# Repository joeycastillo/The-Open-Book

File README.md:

# The Open Book: Project Reboot

**A note from the project creator:** The Open Book was my first real electronics project; the earliest designs date to late 2019. I have learned a lot since those early days, and as such, here three years later, I am hitting reset. At this time the repository contains a version of the Open Book designed around the Raspberry Pi Pico. It's optimized for low part count and easy hand assembly, but it runs on AAA batteries and may not be as svelte as some folks might prefer. At a later date, I hope to design a followup with built-in LiPo charging and a slimmer profile, but at this time, this version of the book is the quickest path to getting hardware in people's hands so that we can start hacking on firmware together.

For details on how to build, test and use Open Book, I've [made documentation available here](https://www.oddlyspecificobjects.com/projects/openbook/).

The original Open Book repository has been archived in a branch called [original](https://github.com/joeycastillo/The-Open-Book/tree/original).

[The Open Book firmware, called libros, is under development here](https://github.com/joeycastillo/libros). It's a goddamn mess in some ways, and in dire need of some documentation, but for the moment it does do the job of presenting a list of books stored on an SD card, and letting you read them. The canonical format for books is plain text with the book title on the first line, OR plain text plus some front matter and some ASCII control codes for chapter breaks and formatting, [as documented here](https://www.oddlyspecificobjects.com/projects/openbook/#advanced-text-formatting).

## Original Introduction

As a society, we need an open source device for reading. Books are among the most important documents of our culture, yet the most popular and widespread devices we have for reading — the Kobo, the Nook, the Kindle and even the iPad — are closed devices, operating as small moving parts in a set of giant closed platforms whose owners' interests are not always aligned with readers'.

The Open Book aims to be a simple device that anyone with a soldering iron can build for themselves. The Open Book should be comprehensible: the reader should be able to look at it and understand, at least in broad strokes, how it works. It should be extensible, so that a reader with different needs can write code and add accessories that make the book work for them. It should be global, supporting readers of books in all the languages of the world. Most of all, it should be open, so that anyone can take this design as a starting point and use it to build a better book.

## State of the Book

At this time, the Pi Pico book is in decent shape if you want to try your hand at building it yourself. You will need to have two custom things fabricated: the **Open Book Main Board** (which you can get as a bare PCB) and the **Castellated E-Paper Driver** module (which you'll want to have done as a PCBA job). All the files you will need to send out for this can be found in the **Fabrication Files** folder in the project root:

* Upload `OSO-BOOK-C1-04-rounded.zip` to your PCB fabrication house of choice. It is designed to be a two-layer, 1 mm thick PCB, and you can use either an ENIG or lead-free HASL finish.
* If you plan to use JLCPCB's economic PCBA service, upload all three files in `OSO-BOOK-C2-01` to JLCPCB. Opt for a 1 mm thick lead-free HASL finish. Note that the board is slightly wider than it needs to be, just to meet the minimum size requirements for this service.
* If you plan to use PCBWay's PCBA service, upload all three files in `OSO-BOOK-C2-02` to PCBWay. Once again, opt for a 1 mm thick lead-free HASL finish. 

Other Parts: 

* Two of these [side mount buttons](https://www.digikey.com/en/products/detail/würth-elektronik/434351045816/5209090)
* One of these [side-mount switches](https://www.digikey.com/en/products/detail/c-k/JS102011SAQN/1640095)
* One [MEM2075 MicroSD card slot](https://www.digikey.com/en/products/detail/gct/MEM2075-00-140-01-A/9859614)
* One [GD25Q16C Flash chip](https://www.digikey.com/en/products/detail/gigadevice-semiconductor-hk-limited/GD25Q16CTIGR/9484675) with SOIC / SOP8 footprint.
* One [Keystone 1022 dual AAA battery holder](https://www.digikey.com/en/products/detail/keystone-electronics/1022/2137859) (you can get clones on Aliexpress for cheap)
* Two P-channel MOSFETS with SOT23 footprint (I use the DMG3415)
* Two 10kΩ resistors with 1206 footprint.
* Two 10µF capacitors with 1206 footprint (rated voltage >=6.3V).
* One 1µF capacitor with 0805 footprint (rated voltage >=6.3V).
* Seven through-hole slim tactile buttons (3mm by 6mm; [TL1107 type](https://www.digikey.com/en/products/detail/e-switch/TL1107AF130WQ/378976))
* One [GDEW042T2 grayscale e-paper display](https://buy-lcd.com/products/42inch-e-inkanel-spi-interface-buy-eaper-display). (Don't get the tri-color version; it'll end in heartbreak)
* And finally, one [Raspberry Pi Pico](https://www.digikey.com/en/products/detail/raspberry-pi/SC0915/13624793) board

The Open Book is open source hardware: you should feel free to build one yourself, order parts for ten and do a workshop at your local maker space, or even buy parts for fifty and sell them as kits. 

Please steal this book.

I plan to add more documentation in the new year, but until then, [this half-hour video walks through building one Open Book board in real-time](https://archive.org/details/live-from-the-oddly-specific-kitchen-table-assembling-the-pcbway-official-sponso).

### Forking and tweaking the boards

* Design files for the Open Book main board can be found in the `OSO-BOOK-C1` folder. It's a KiCad project.
* Design files for the castellated e-paper driver module can be found in the `OSO-BOOK-C2` folder. Alas, they are Eagle projects that predate my move to KiCad. There are two versions: an older version that was successfully fabricated with JLCPCB's economic PCBA service (`OSO-BOOK-C2-01`), and a newer version successfully fabricated using PCBWay's PCBA service (`OSO-BOOK-C2-02`). Both work great.

## License

 Different components of the project are licensed differently, see [LICENSE.md](https://github.com/joeycastillo/The-Open-Book/blob/main/LICENSE.md).

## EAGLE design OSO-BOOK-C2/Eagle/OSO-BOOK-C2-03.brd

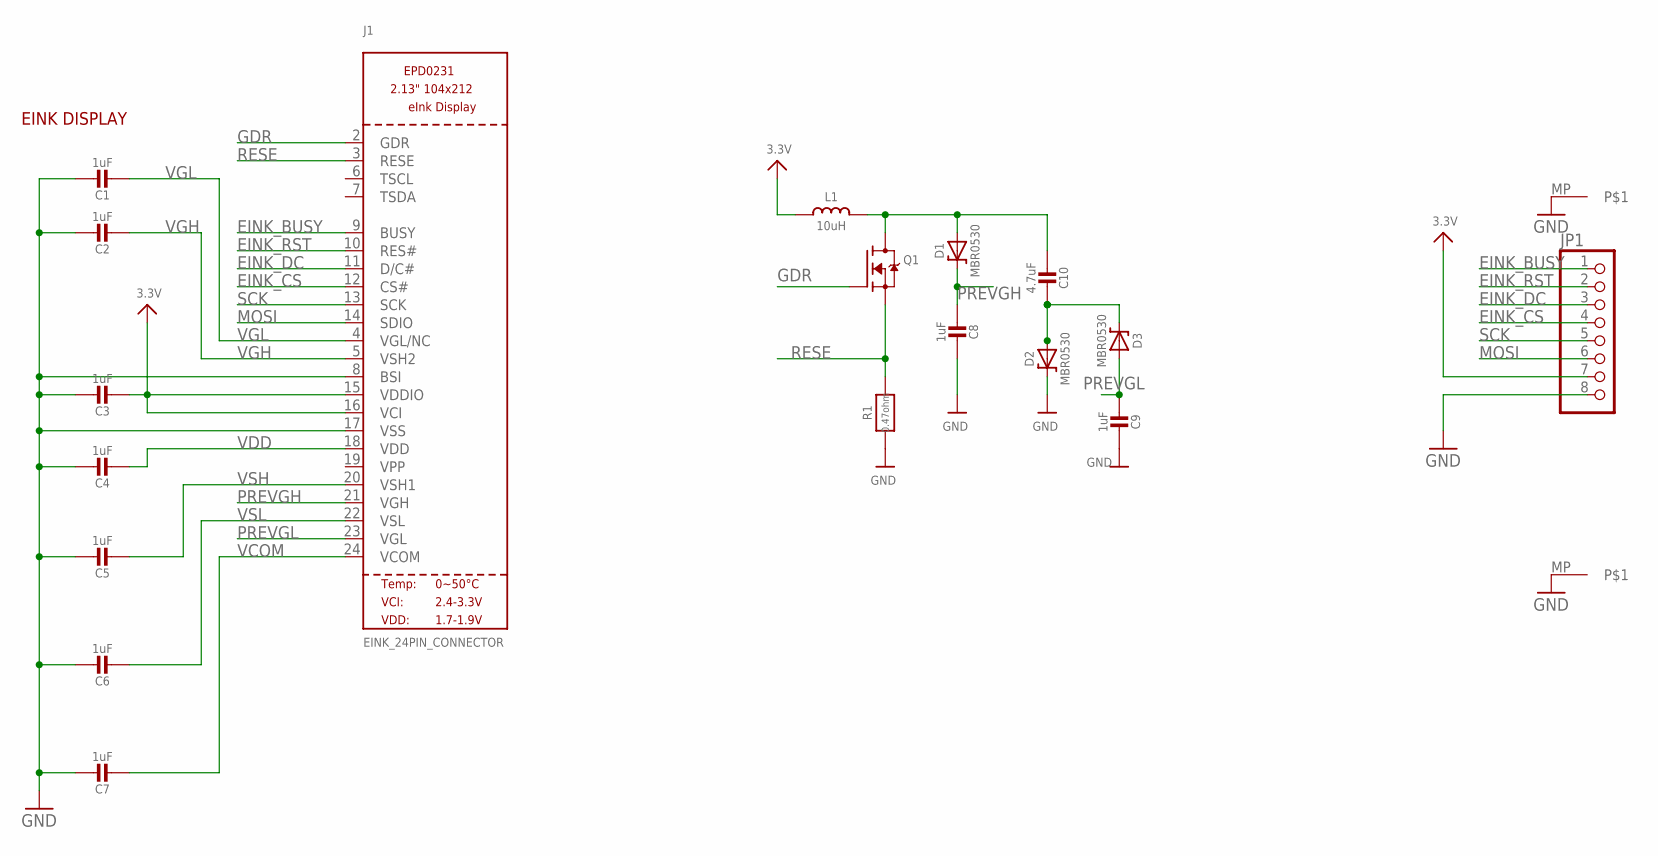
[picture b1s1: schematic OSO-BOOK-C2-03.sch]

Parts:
C1, C2, C3, C4, C5, C6, C7, C8, C9: 1uF; 0805-NO
C10: 4.7uF; 0805-NO
D1, D2, D3: MBR0530; SOD-123
J1: EINK_24PIN_CONNECTOR; EINK_24PIN
JP1: HEADER-1X8ROUND76; 1X08_ROUND_76
L1: 10uH; MICROBUILDER__0805
Q1: IRLML0100; SOT23-3
R1: 0.47ohm; _0402
U$2, U$3: BIGOVAL

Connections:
3.3V: C3.2, J1.15 (VDDIO), J1.16 (VCI), JP1.7, L1.1
EINK_BUSY: J1.9 (BUSY), JP1.1
EINK_CS: J1.12 (CS#), JP1.4
EINK_DC: J1.11 (D/C#), JP1.3
EINK_RST: J1.10 (RES#), JP1.2
GDR: J1.2 (GDR), Q1.1 (G)
GND: C1.1, C2.1, C3.1, C4.1, C5.1, C6.1, C7.1, C8.2, C9.2, D2.C, J1.8 (BSI), J1.17 (VSS), JP1.8, R1.2, U$2.MP, U$3.MP
MOSI: J1.14 (SDIO), JP1.6
unnamed: C10.2, D2.A, D3.C
unnamed: C10.1, D1.A, L1.2, Q1.3 (D)
PREVGH: C8.1, D1.C, J1.21 (VGH)
PREVGL: C9.1, D3.A, J1.23 (VGL)
RESE: J1.3 (RESE), Q1.2 (S), R1.1
SCK: J1.13 (SCK), JP1.5
VCOM: C7.2, J1.24 (VCOM)
VDD: C4.2, J1.18 (VDD)
VGH: C2.2, J1.5 (VSH2)
VGL: C1.2, J1.4 (VGL/NC)
VSH: C5.2, J1.20 (VSH1)
VSL: C6.2, J1.22 (VSL)

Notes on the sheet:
EINK DISPLAY

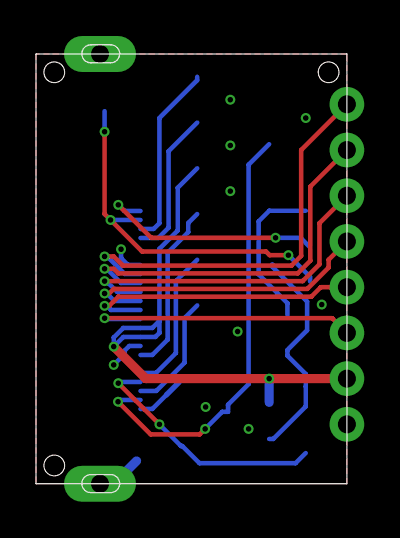
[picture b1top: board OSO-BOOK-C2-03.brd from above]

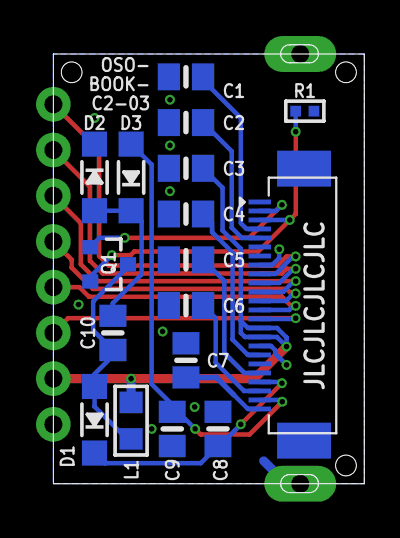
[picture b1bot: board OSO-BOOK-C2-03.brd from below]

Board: 2 copper layers, 17.3 x 24.9 mm, 20 parts (17 on the bottom side), 20 nets.

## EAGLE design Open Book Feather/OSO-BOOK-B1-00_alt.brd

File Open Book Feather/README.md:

# Notes on the Open Book PCB files

The current working, tested revision is **Open Book A1 Rev 06** (**OSO-BOOK-A1-06**). For the sake of clarity, I've removed revisions 01 through 04; if you made one of these old boards, these notes remain.

## Open Book A1 Rev 01 Errata

I imagine you don't have this board; it was the first test, and was replaced with revision 2 almost immediately. It had a couple of big issues:

* The buttons on the shift register floated, because there were no pull-up resistors. This rendered the buttons unusable.
* The Neopixel, in addition to being in a really inconvenient place, was powered by VHI instead of the 3V regulator, which made it power up before everything else and shine bright blue until you took control of it. It also wouldn't turn off when the enable switch was thrown.

## Open Book A1 Rev 02 Errata

There are two errors on this revision's descriptive silkscreen: first, at the bottom, in the "Button Register" block, the shift register's pins are listed as:

    Pins: 
    BUTTON_LATCH: D48/PB31
    BUTTON_OUT:  D49/PB30
    BUTTON_CLOCK: D50/PB00

The correct mapping is:

    Pins: 
    BUTTON_LATCH: D50/PB00
    BUTTON_OUT:  D49/PB30
    BUTTON_CLOCK: D48/PB31

Second, the SAM D51 Microcontroller block erroneously lists the UART's SERCOM as SERCOM0. It is in fact SERCOM5.

## Open Book A1 Rev 03

Revision 3 was never fabricated; it simply fixed the first error above, but was otherwise identical to Revision 2. I wanted to correct the error in case anyone was building along at home, and bumped the revision to make it clear which version had the issue. It still has the incorrect SERCOM listed, though; that was not caught until later.

Note that the pin muxing changed after revision 3; if you have board revision A1-01, A1-02 or A1-03, you will need to set a flag when compiling your code. In the Arduino IDE, this setting is in `Tools -> Hardware Revision`. In CircuitPython, you can just use the digital pin numbers as labeled on your silkscreen to access the correct pins.

## Open Book A1 Rev 04

This board has the final pinout (no need to set the Hardware Revision flag), and adds several features:

* Microphone shutdown pin
* USB voltage monitor (detect when plugged in to external power)
* Battery full indicator

This is the last revision with the SERCOM0/SERCOM5 silkscreen error.

## Open Book A1 Rev 05

This is identical to Rev 04, but fixes the silkscreen error in the SAM D51 block. It also adds a RC filter to the USB cable shield (recommendation from the SAM D51 data sheet), and tweaks the through-hole button footprints for a slightly better fit.

This version works quite well. If you have this version, there is no need to get the A1-06 version.

## Open Book A1 Rev 06

This is the final version of the A1-type hardware. It adds pull-up resistors for the Babel Flash chip and MicroSD card, and bias resistors for the audio output on the headphone jack.

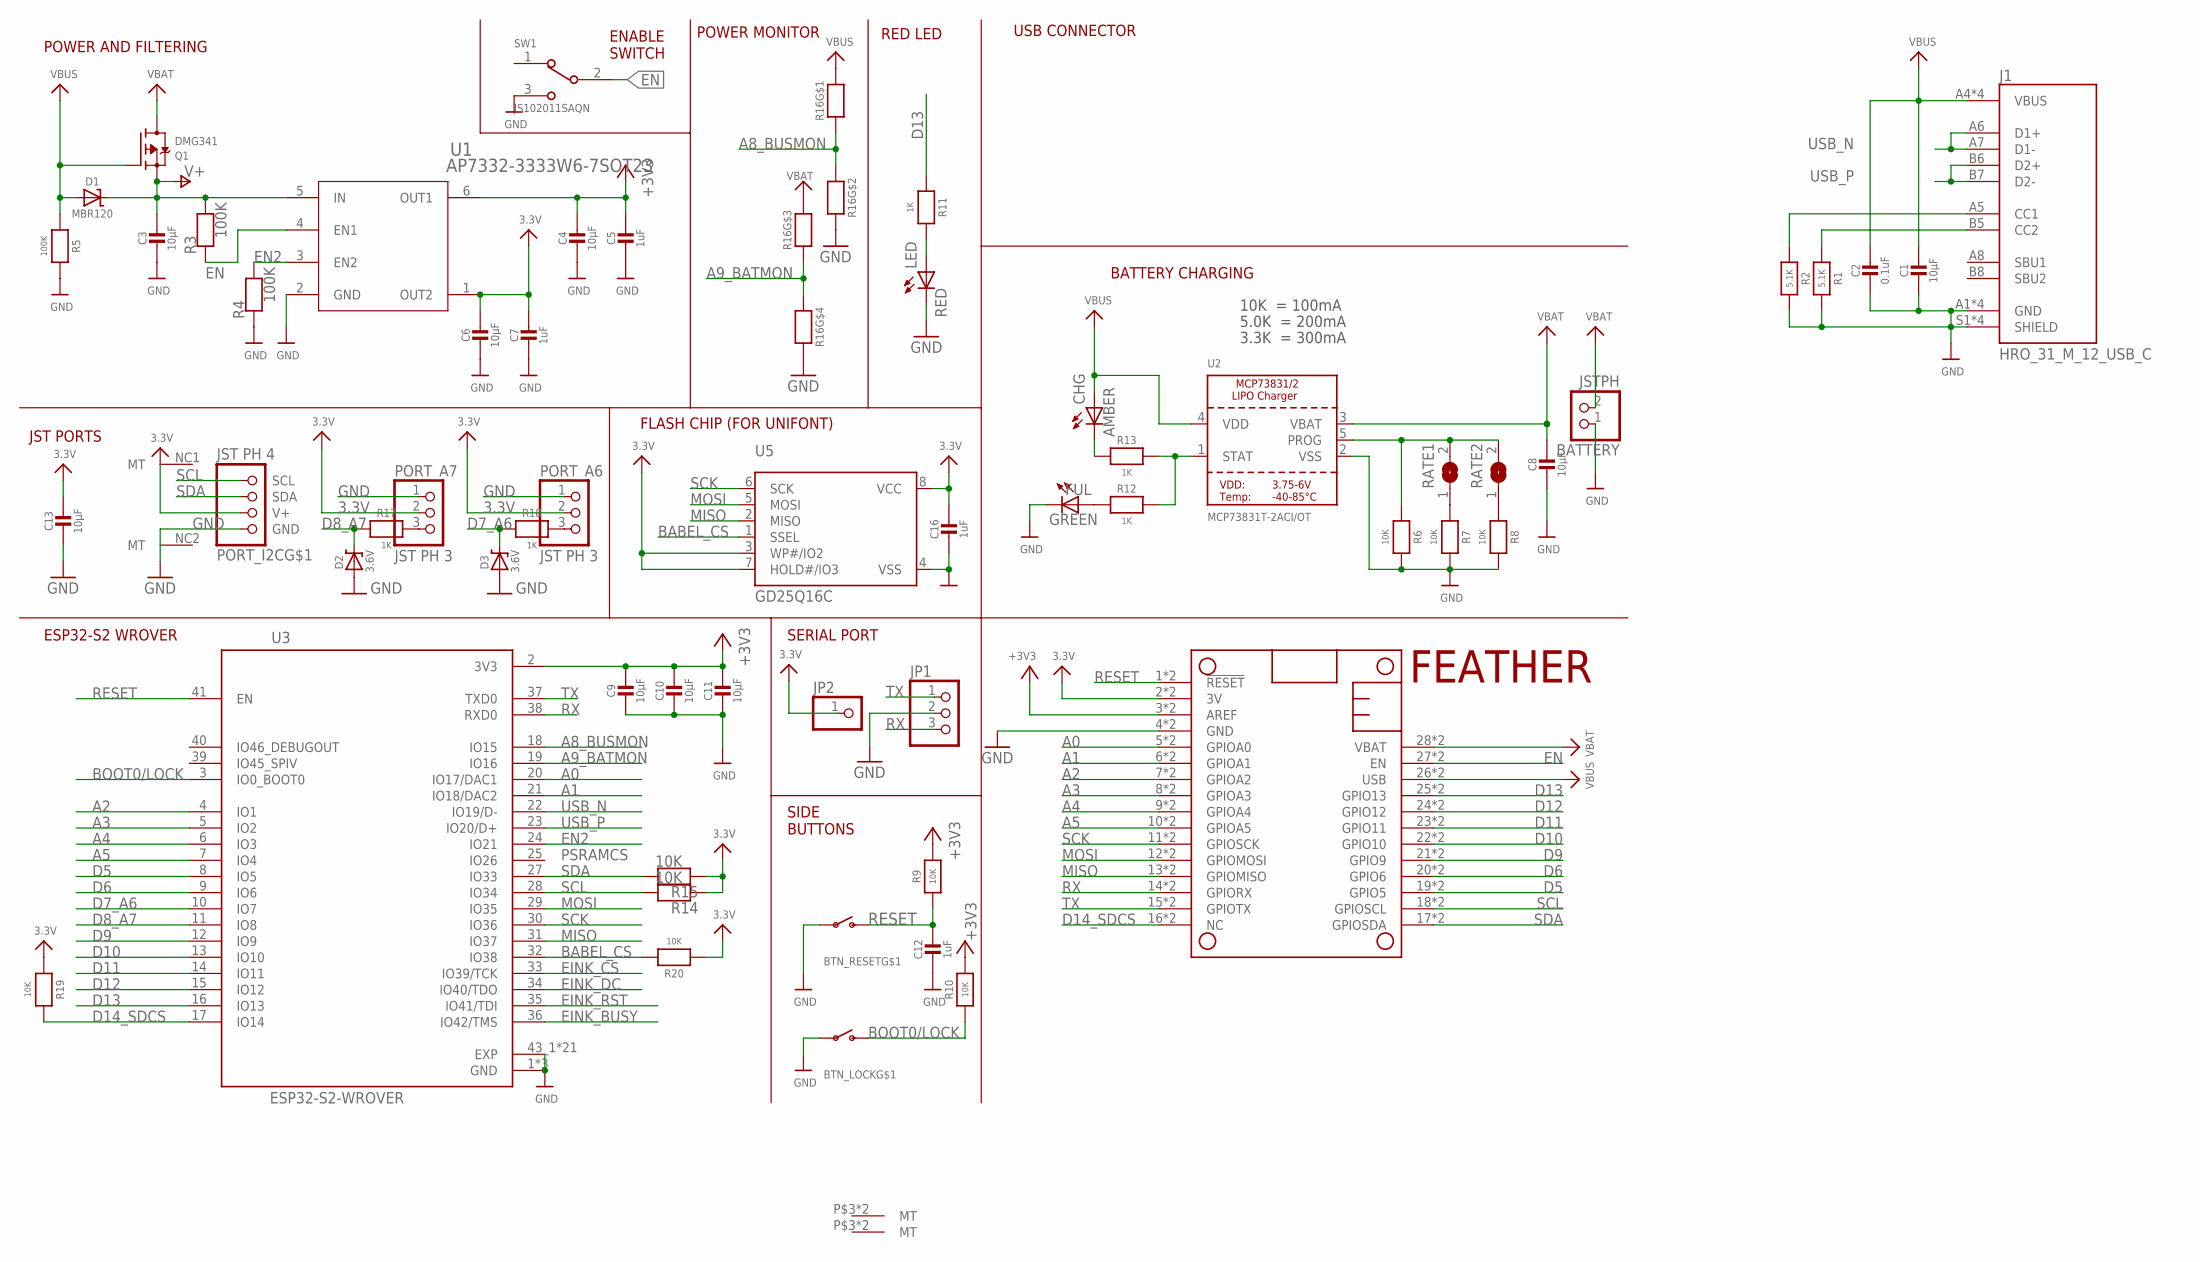
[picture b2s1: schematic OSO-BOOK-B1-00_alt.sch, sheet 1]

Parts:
BATTERY: JSTPH; JSTPH2
BTN_LOCK: SWITCH_SPSTTL3330A; TL3330A
BTN_RESET: SWITCH_SPSTTL3330A; TL3330A
C1, C3, C4, C6, C8, C9, C10, C11, C13: 10µF; 0805-NO
C2: 0.1uF; 0805-NO
C5, C7, C12, C16: 1uF; 0805-NO
CHG: AMBER; CHIP-LED0805
D1: MBR120; SOD-123
D2, D3: 3.6V; SOD-123
FUL: GREEN; CHIP-LED0805
J1: HRO_31_M_12_USB_C
JP1: PINHD-1X3; 1X03
JP2: PINHD-1X1; 1X01
LED: RED; CHIP-LED0805
MS1: FEATHERWING_SMTDUALNOHOLES; FEATHERWING_SMT_NOHOLES
PORT_A6, PORT_A7: JST PH 3; JSTPH3
PORT_I2C: JST PH 4; JSTPH4
Q1: DMG341; SOT23-R
R1, R2: 5.1K; 0805-NO
R3, R4, R5: 100K; 0805-NO
R6, R7, R8, R9, R10, R14, R15, R19, R20: 10K; 0805-NO
R11, R12, R13, R17, R18: 1K; 0805-NO
R16: EXB-V8V103JV-GOOD; EXBV8V
RATE1, RATE2: SOLDERJUMPER; SOLDERJUMPER_ARROW_NOPASTE
SW1: JS102011SAQN; SW_JS102011SAQN
U1: AP7332-3333W6-7SOT23; SOT23-6
U2: MCP73831T-2ACI/OT; SOT23-5
U3: ESP32-S2-WROVER; MODULE_ESP32-S2-WROVER
U5: GD25Q16C; MICROBUILDER_SOIC8_150MIL

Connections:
3.3V: C6.1, C7.1, C13.1, C16.1, JP2.1, MS1.2 (3V), MS1.2B (3V), PORT_A6.2, PORT_A7.2, PORT_I2C.2 (V+), R14.1, R15.1, R19.1, R20.1, U1.1 (OUT2), U5.3 (WP#/IO2), U5.7 (HOLD#/IO3), U5.8 (VCC); also elsewhere on the board
+3V3: C4.1, C5.1, C9.1, C10.1, C11.1, MS1.3 (AREF), MS1.3B (AREF), R9.2, R10.2, U1.6 (OUT1), U3.2 (3V3)
A0: MS1.5 (GPIOA0), MS1.5B (GPIOA0), U3.20 (IO17/DAC1)
A1: MS1.6 (GPIOA1), MS1.6B (GPIOA1), U3.21 (IO18/DAC2)
A2: MS1.7 (GPIOA2), MS1.7B (GPIOA2), U3.4 (IO1)
A3: MS1.8 (GPIOA3), MS1.8B (GPIOA3), U3.5 (IO2)
A4: MS1.9 (GPIOA4), MS1.9B (GPIOA4), U3.6 (IO3)
A5: MS1.10 (GPIOA5), MS1.10B (GPIOA5), U3.7 (IO4)
A6: PORT_A6.3, R18.1
A7: PORT_A7.3, R17.1
A8_BUSMON: R16.1, R16.2 (1), U3.18 (IO15)
A9_BATMON: R16.3 (1), R16.4 (1), U3.19 (IO16)
BABEL_CS: R20.2, U3.32 (IO38), U5.1 (SSEL)
BOOT0/LOCK: BTN_LOCK.P$2 (S), R10.1, U3.3 (IO0_BOOT0)
D5: MS1.19 (GPIO5), MS1.19B (GPIO5), U3.8 (IO5)
D6: MS1.20 (GPIO6), MS1.20B (GPIO6), U3.9 (IO6)
D7_A6: D3.C, R18.2, U3.10 (IO7)
D8_A7: D2.C, R17.2, U3.11 (IO8)
D9: MS1.21 (GPIO9), MS1.21B (GPIO9), U3.12 (IO9)
D10: MS1.22 (GPIO10), MS1.22B (GPIO10), U3.13 (IO10)
D11: MS1.23 (GPIO11), MS1.23B (GPIO11), U3.14 (IO11)
D12: MS1.24 (GPIO12), MS1.24B (GPIO12), U3.15 (IO12)
D13: MS1.25 (GPIO13), MS1.25B (GPIO13), R11.1, U3.16 (IO13)
D14_SDCS: MS1.16 (NC), MS1.16B (NC), R19.2, U3.17 (IO14); also elsewhere on the board
EINK_BUSY: U3.36 (IO42/TMS); also elsewhere on the board
EINK_CS: U3.33 (IO39/TCK); also elsewhere on the board
EINK_DC: U3.34 (IO40/TDO); also elsewhere on the board
EINK_RST: U3.35 (IO41/TDI); also elsewhere on the board
EN: MS1.27 (EN), MS1.27B (EN), R3.1, SW1.2, U1.4 (EN1)
EN2: R4.2, U1.3 (EN2), U3.24 (IO21)
GND: BATTERY.1, BTN_LOCK.P$1, BTN_RESET.P$1, C1.2, C2.2, C3.2, C4.2, C5.2, C6.2, C7.2, C8.2, C9.2, C10.2, C11.2, C12.2, C13.2, C16.2, D2.A, D3.A, FUL.C, J1.A1 (GND), J1.A12 (GND), J1.B1 (GND), J1.B12 (GND), J1.S1 (SHIELD), J1.S2 (SHIELD), J1.S3 (SHIELD), J1.S4 (SHIELD), JP1.2, LED.C, MS1.4 (GND), MS1.4B (GND), PORT_A6.1, PORT_A7.1, PORT_I2C.1 (GND), R1.2, R2.2, R4.1, R5.2, R6.2, R7.2, R8.2, R16.5 (2), R16.7 (2), SW1.3, U1.2 (GND), U2.2 (VSS), U3.1 (GND), U3.26 (GND), U3.42 (GND), U3.43_1 (EXP), U3.43_2 (EXP), U3.43_3 (EXP), U3.43_4 (EXP), U3.43_5 (EXP), U3.43_6 (EXP), U3.43_7 (EXP), U3.43_8 (EXP), U3.43_9 (EXP), U3.43_10 (EXP), U3.43_11 (EXP), U3.43_12 (EXP), U3.43_13 (EXP), U3.43_14 (EXP), U3.43_15 (EXP), U3.43_16 (EXP), U3.43_17 (EXP), U3.43_18 (EXP), U3.43_19 (EXP), U3.43_20 (EXP), U3.43_21 (EXP), U5.4 (VSS); also elsewhere on the board
MISO: MS1.13 (GPIOMISO), MS1.13B (GPIOMISO), U3.31 (IO37), U5.2 (MISO); also elsewhere on the board
MOSI: MS1.12 (GPIOMOSI), MS1.12B (GPIOMOSI), U3.29 (IO35), U5.5 (MOSI); also elsewhere on the board
unnamed: R7.1, RATE1.1
unnamed: CHG.C, R13.1
unnamed: R8.1, RATE2.1
unnamed: LED.A, R11.2
unnamed: FUL.A, R12.1
unnamed: J1.B5 (CC2), R1.1
unnamed: J1.A5 (CC1), R2.1
PROG: R6.1, RATE1.2, RATE2.2, U2.5 (PROG)
RESET: BTN_RESET.P$2 (S), C12.1, MS1.1 (!RESET), MS1.1B (!RESET), R9.1, U3.41 (EN)
RX: JP1.3, MS1.14 (GPIORX), MS1.14B (GPIORX), U3.38 (RXD0)
SCK: MS1.11 (GPIOSCK), MS1.11B (GPIOSCK), U3.30 (IO36), U5.6 (SCK); also elsewhere on the board
SCL: MS1.18 (GPIOSCL), MS1.18B (GPIOSCL), PORT_I2C.4 (SCL), R14.2, U3.28 (IO34); also elsewhere on the board
SDA: MS1.17 (GPIOSDA), MS1.17B (GPIOSDA), PORT_I2C.3 (SDA), R15.2, U3.27 (IO33); also elsewhere on the board
STAT: R12.2, R13.2, U2.1 (STAT)
TX: JP1.1, MS1.15 (GPIOTX), MS1.15B (GPIOTX), U3.37 (TXD0)
USB_N: J1.A6 (D1+), J1.A7 (D1-), U3.22 (IO19/D-)
USB_P: J1.B6 (D2+), J1.B7 (D2-), U3.23 (IO20/D+)
V+: C3.1, D1.C, Q1.2 (S), R3.2, U1.5 (IN)
VBAT: BATTERY.2, C8.1, MS1.28 (VBAT), MS1.28B (VBAT), Q1.3 (D), R16.6 (2), U2.3 (VBAT)
VBUS: C1.1, C2.1, CHG.A, D1.A, J1.A4 (VBUS), J1.A9 (VBUS), J1.B4 (VBUS), J1.B9 (VBUS), MS1.26 (USB), MS1.26B (USB), Q1.1 (G), R5.1, R16.8 (2), U2.4 (VDD)

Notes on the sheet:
FEATHER
POWER AND FILTERING
10K = 100mA
5.0K = 200mA
3.3K = 300mA
BATTERY CHARGING
USB CONNECTOR
POWER MONITOR
PSRAMCS
FLASH CHIP (FOR UNIFONT)
SERIAL PORT
RED LED
ENABLE SWITCH
SIDE BUTTONS
JST PORTS
ESP32-S2 WROVER

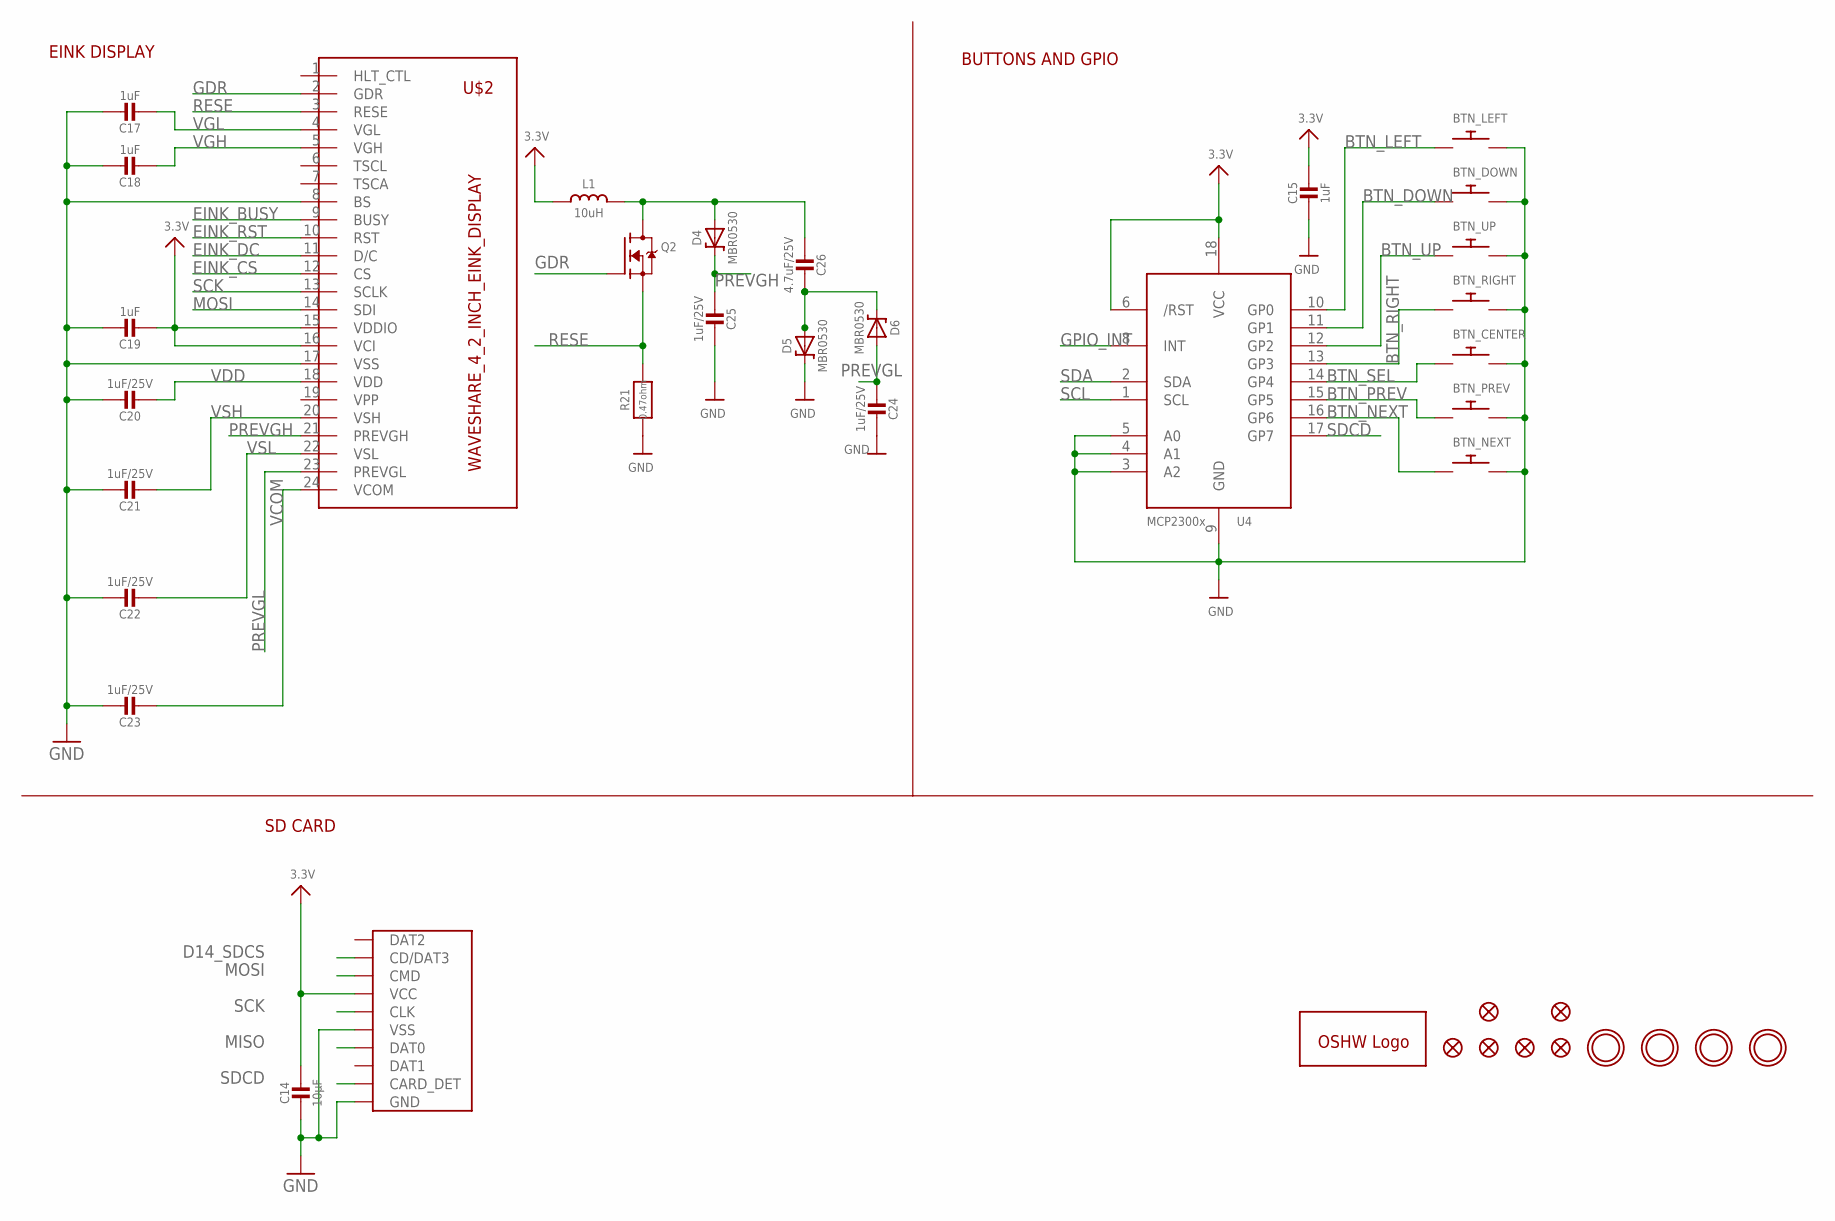
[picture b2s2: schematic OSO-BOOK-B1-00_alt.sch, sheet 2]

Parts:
BTN_CENTER: SWITCH_PUSHBUTTON_3.5X6MM; TACTILE_3X6MM
BTN_DOWN: SWITCH_PUSHBUTTON_3.5X6MM; TACTILE_3X6MM
BTN_LEFT: SWITCH_PUSHBUTTON_3.5X6MM; TACTILE_3X6MM
BTN_NEXT: SWITCH_PUSHBUTTON_3.5X6MM; TACTILE_3X6MM
BTN_PREV: SWITCH_PUSHBUTTON_3.5X6MM; TACTILE_3X6MM
BTN_RIGHT: SWITCH_PUSHBUTTON_3.5X6MM; TACTILE_3X6MM
BTN_UP: SWITCH_PUSHBUTTON_3.5X6MM; TACTILE_3X6MM
C14: 10µF; 0805-NO
C15, C17, C18, C19: 1uF; 0805-NO
C20, C21, C22, C23, C24, C25: 1uF/25V; 0805-NO
C26: 4.7uF/25V; 0805-NO
D4, D5, D6: MBR0530; SOD-123
FID1, FID2, FID3, FID4, FID5, FID6: FIDUCIAL_1MM
GOLD_ORB_SM1: OSHWLOGOLOGO5MM; OSHW_5MM
L1: 10uH; MICROBUILDER_INDUCTOR_4X4MM_NR401_BIGPADS
Q2: IRLML0100; SOT23-3
R21: 0.47ohm; 0805-NO
U4: MCP23008/SO; SO18W
U$1, U$4, U$5, U$7: MOUNTINGHOLE2.5; MOUNTINGHOLE_2.5_PLATED
U$2: WAVESHARE_4_2_INCH_EINK_DISPLAY; EINK_DISPLAY_4_2IN
U$23: MICRO_SD_CARD_; TFP09-2--12B

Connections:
3.3V: C14.1, C15.1, C19.2, L1.P$1 (1), U4.6 (/RST), U4.18 (VCC), U$2.15 (VDDIO), U$2.16 (VCI), U$23.VCC; also elsewhere on the board
BTN_DOWN: BTN_DOWN.P$1, U4.11 (GP1)
BTN_LEFT: BTN_LEFT.P$1, U4.10 (GP0)
BTN_NEXT: BTN_NEXT.P$1, U4.16 (GP6)
BTN_PREV: BTN_PREV.P$1, U4.15 (GP5)
BTN_RIGHT: BTN_RIGHT.P$1, U4.13 (GP3)
BTN_SEL: BTN_CENTER.P$1, U4.14 (GP4)
BTN_UP: BTN_UP.P$1, U4.12 (GP2)
D14_SDCS: U$23.CD/DAT3; also elsewhere on the board
EINK_BUSY: U$2.9 (BUSY); also elsewhere on the board
EINK_CS: U$2.12 (CS); also elsewhere on the board
EINK_DC: U$2.11 (D/C); also elsewhere on the board
EINK_RST: U$2.10 (RST); also elsewhere on the board
GDR: Q2.1 (G), U$2.2 (GDR)
GND: BTN_CENTER.P$2, BTN_DOWN.P$2, BTN_LEFT.P$2, BTN_NEXT.P$2, BTN_PREV.P$2, BTN_RIGHT.P$2, BTN_UP.P$2, C14.2, C15.2, C17.1, C18.1, C19.1, C20.1, C21.1, C22.1, C23.1, C24.2, C25.2, D5.C, R21.2, U4.3 (A2), U4.4 (A1), U4.5 (A0), U4.9 (GND), U$2.8 (BS), U$2.17 (VSS), U$23.GND, U$23.GND@1 (GND), U$23.GND@2 (GND), U$23.GND@3 (VSS), U$23.VSS (GND); also elsewhere on the board
GPIO_INT: U4.8 (INT)
MISO: U$23.DAT0; also elsewhere on the board
MOSI: U$2.14 (SDI), U$23.CMD; also elsewhere on the board
unnamed: C26.2, D5.A, D6.C
unnamed: C26.1, D4.A, L1.P$2 (2), Q2.3 (D)
PREVGH: C25.1, D4.C, U$2.21 (PREVGH)
PREVGL: C24.1, D6.A, U$2.23 (PREVGL)
RESE: Q2.2 (S), R21.1, U$2.3 (RESE)
SCK: U$2.13 (SCLK), U$23.CLK; also elsewhere on the board
SCL: U4.1 (SCL); also elsewhere on the board
SDA: U4.2 (SDA); also elsewhere on the board
SDCD: U4.17 (GP7), U$23.CD (CARD_DET)
VCOM: C23.2, U$2.24 (VCOM)
VDD: C20.2, U$2.18 (VDD)
VGH: C18.2, U$2.5 (VGH)
VGL: C17.2, U$2.4 (VGL)
VSH: C21.2, U$2.20 (VSH)
VSL: C22.2, U$2.22 (VSL)

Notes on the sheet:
SD CARD
EINK DISPLAY
BUTTONS AND GPIO

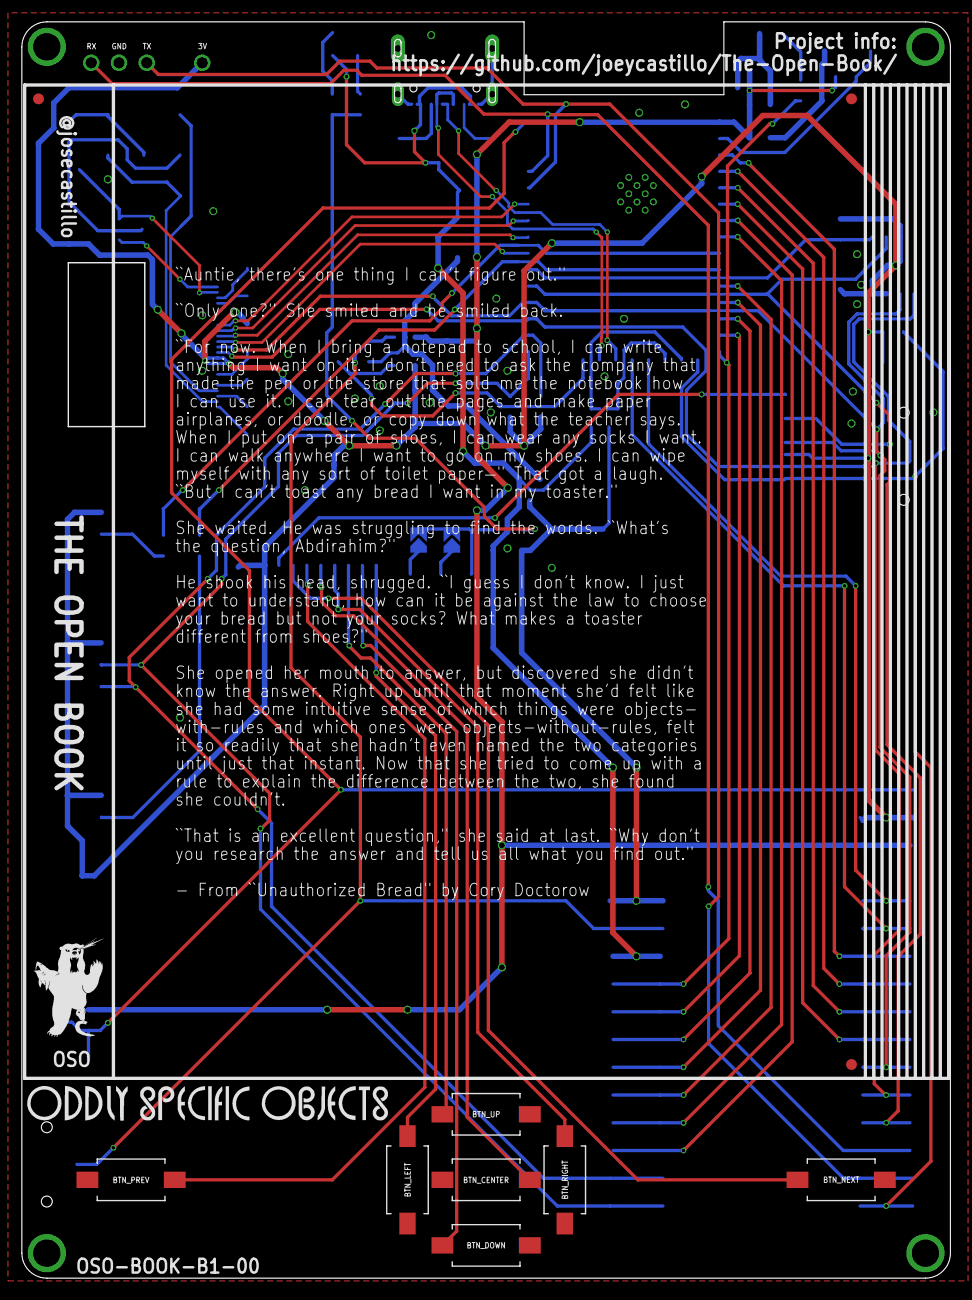
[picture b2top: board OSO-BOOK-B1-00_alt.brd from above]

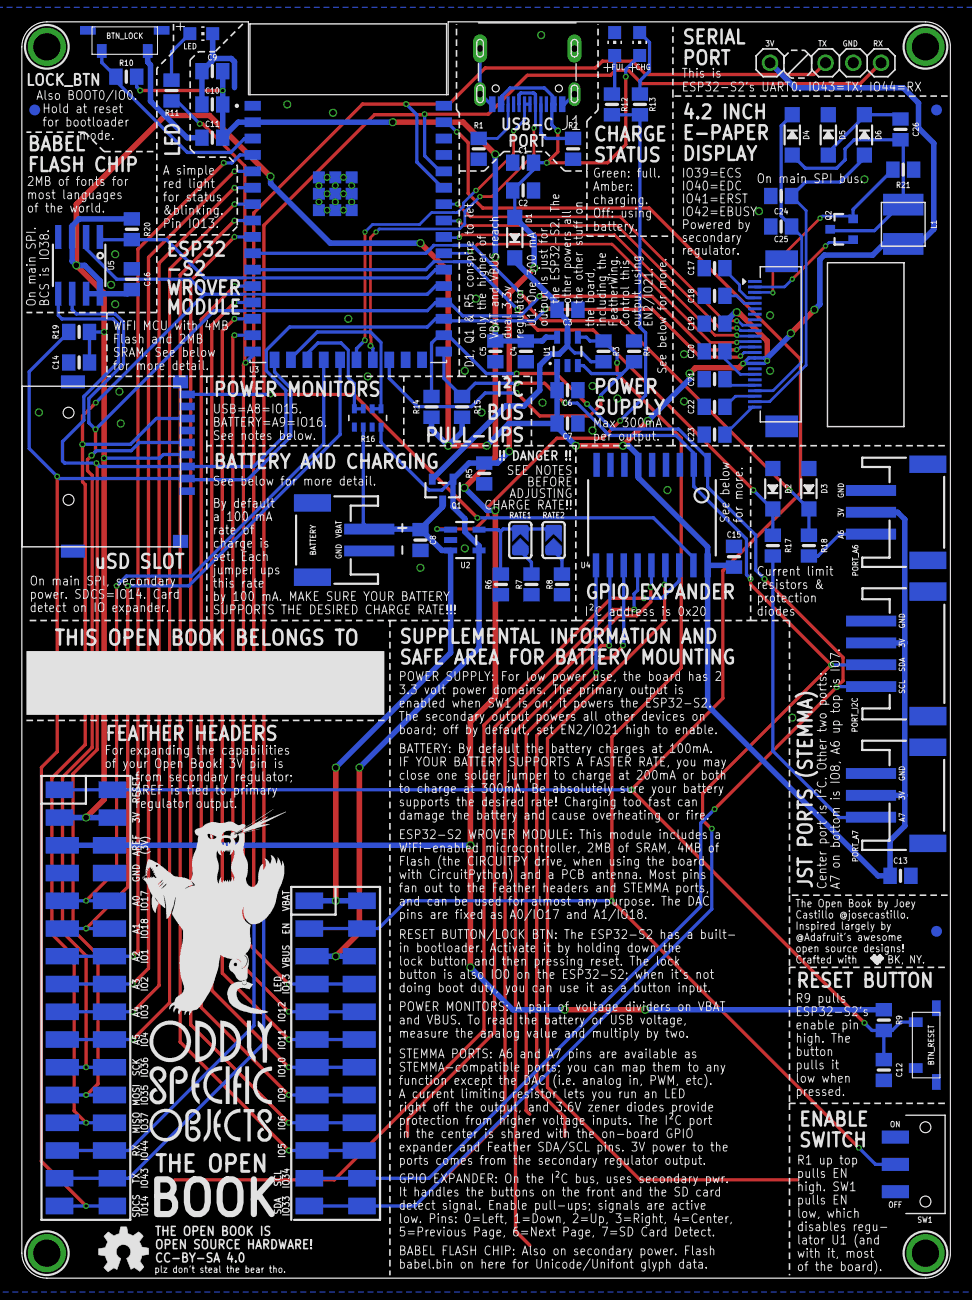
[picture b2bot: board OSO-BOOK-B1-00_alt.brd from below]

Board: 2 copper layers, 85.0 x 115.0 mm, 101 parts (88 on the bottom side), 73 nets.

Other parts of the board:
U$45: OSO_WORDMARK_125X1300MIL_1000DPI
U$47: OSO_BEAR_525X750MIL_1000DPI
U$49: OSO_WORDMARK_THREELINE_450MIL_1000DPI
U$65: OSO_BEAR_250X360MIL_1000DPI

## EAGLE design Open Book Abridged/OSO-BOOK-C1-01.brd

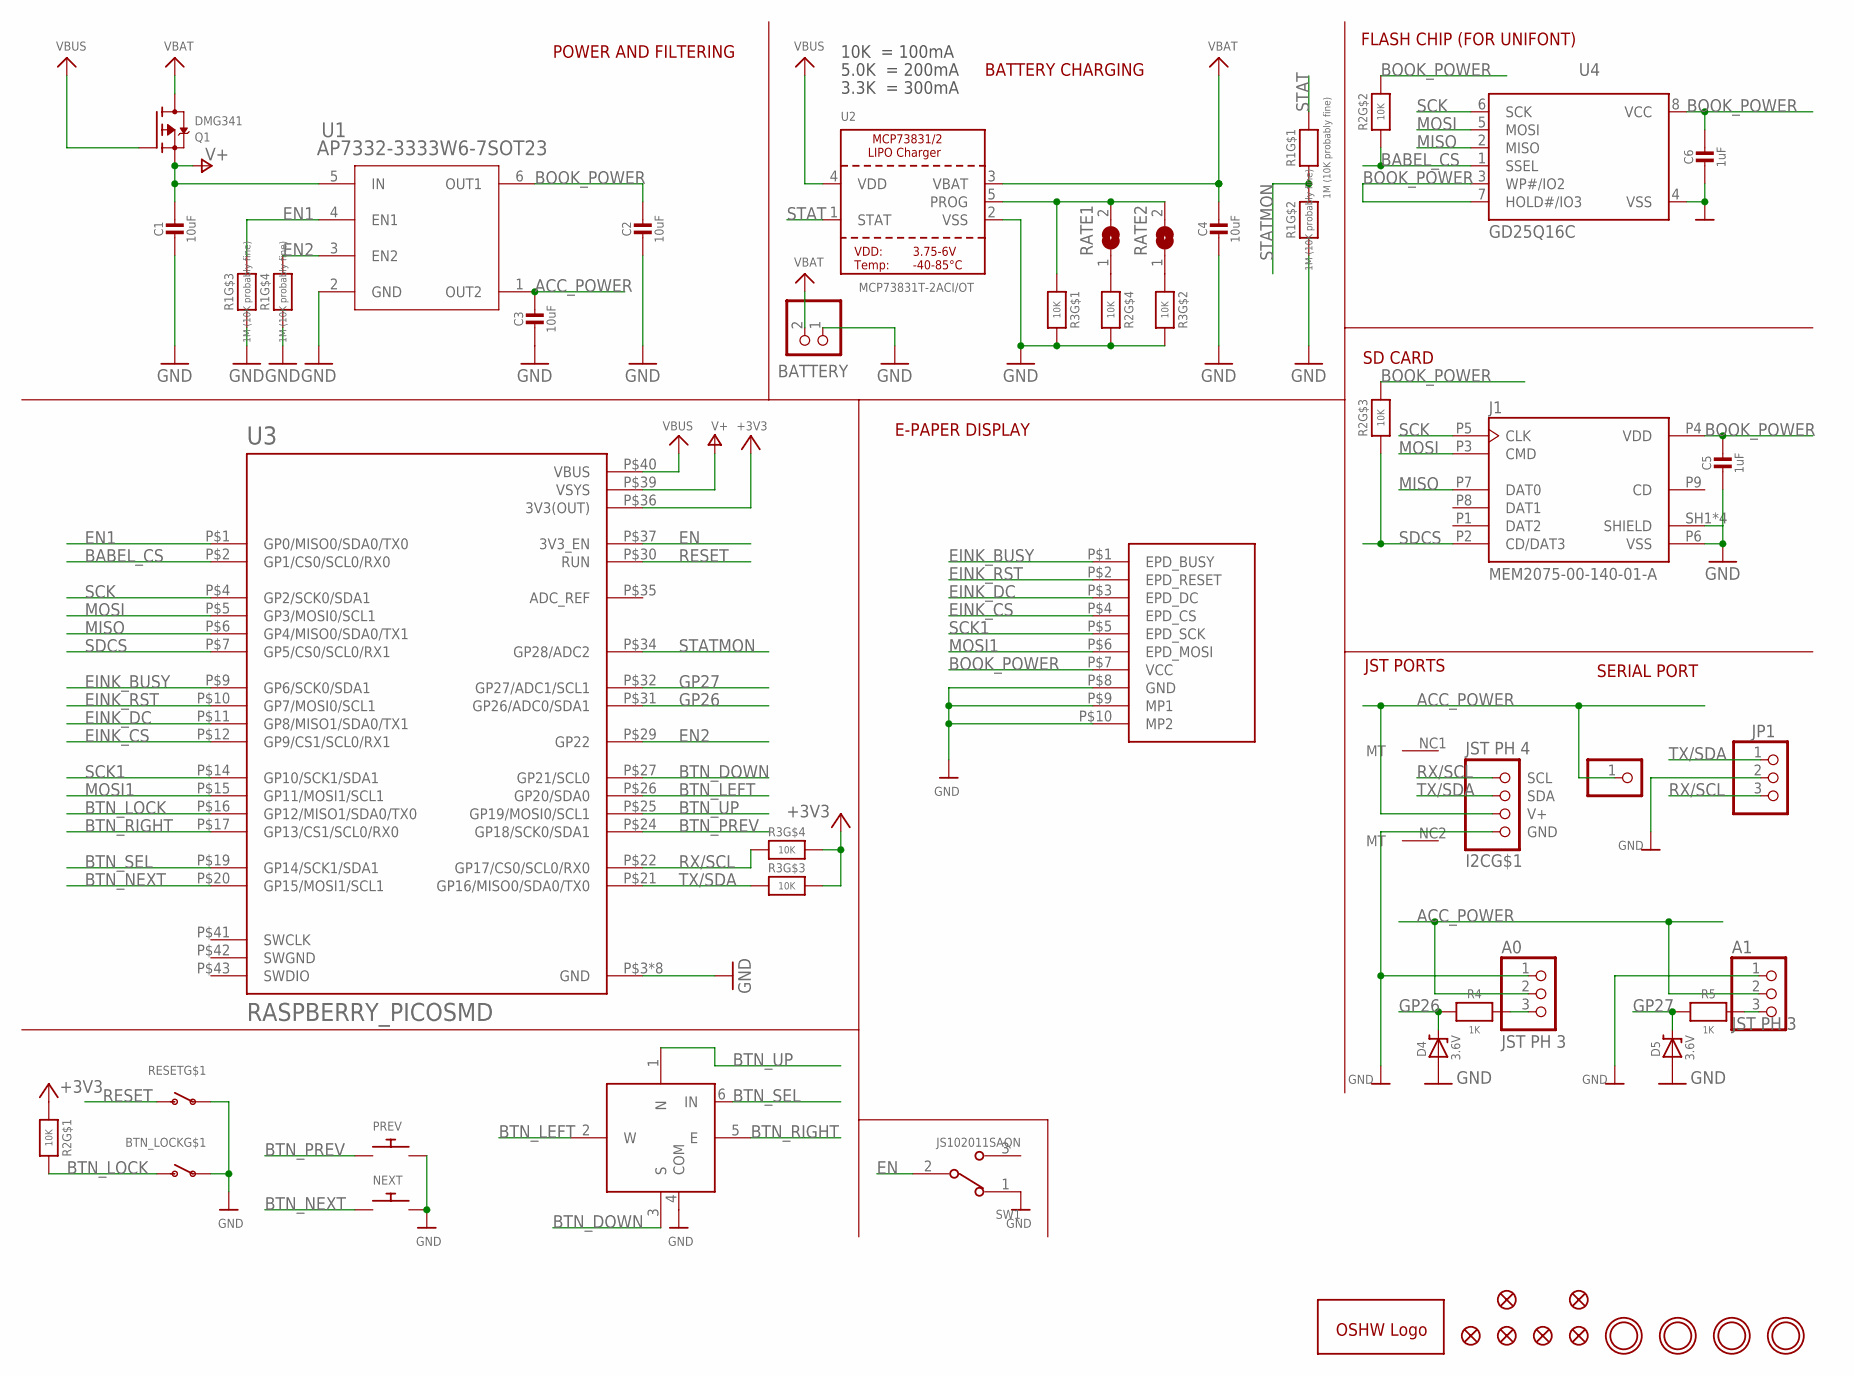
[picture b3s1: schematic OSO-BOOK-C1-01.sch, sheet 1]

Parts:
A0, A1: JST PH 3; JSTPH3
BATTERY: JSTPH; JSTPH2
BTN_LOCK: SWITCH_SPSTTL3330A; TL3330A
C1, C2, C3, C4: 10uF; 0805-NO
C5, C6: 1uF; 0805-NO
D4, D5: 3.6V; SOD-123
FID1, FID2, FID3, FID4, FID5, FID6: FIDUCIAL_1MM
GOLD_ORB_SM1: OSHWLOGOLOGO5MM; OSHW_5MM
I2C: JST PH 4; JSTPH4
J1: MEM2075-00-140-01-A; GCT_MEM2075-00-140-01-A
JP1: PINHD-1X3; 1X03
JP2: PINHD-1X1; 1X01
NEXT: SWITCH_PUSHBUTTON_3.5X6MM; TACTILE_3X6MM
PREV: SWITCH_PUSHBUTTON_3.5X6MM; TACTILE_3X6MM
Q1: DMG341; SOT23-R
R1: 1M (10K probably fine); EXBV8V
R2, R3: 10K; EXBV8V
R4, R5: 1K; 0805-NO
RATE1, RATE2: SOLDERJUMPER; SOLDERJUMPER_ARROW_NOPASTE
RESET: SWITCH_SPSTTL3330A; TL3330A
SW1: JS102011SAQN; SW_JS102011SAQN
SW2: NAVSWITCHSKQUABAUE010; SKQUBAE010
U1: AP7332-3333W6-7SOT23; SOT23-6
U2: MCP73831T-2ACI/OT; SOT23-5
U3: RASPBERRY_PICOSMD; PICO-PKG-SMD
U4: GD25Q16C; MICROBUILDER_SOIC8_150MIL
U$1, U$4, U$5, U$7: MOUNTINGHOLE2.5; MOUNTINGHOLE_2.5_PLATED
U$11: OSO-BOOK-C2-01

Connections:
+3V3: R2.1, R3.5 (2), R3.6 (2), U3.P$36 (3V3(OUT))
ACC_POWER: A0.2, A1.2, C3.1, I2C.2 (V+), JP2.1, U1.1 (OUT2)
BABEL_CS: R2.2 (1), U3.P$2 (GP1/CS0/SCL0/RX0), U4.1 (SSEL)
BOOK_POWER: C2.1, C5.1, C6.1, J1.P4 (VDD), R2.6 (2), R2.7 (2), U1.6 (OUT1), U4.3 (WP#/IO2), U4.7 (HOLD#/IO3), U4.8 (VCC), U$11.P$7 (VCC)
BTN_DOWN: SW2.3 (S), U3.P$27 (GP21/SCL0)
BTN_LEFT: SW2.2 (W), U3.P$26 (GP20/SDA0)
BTN_LOCK: BTN_LOCK.P$2 (S), R2.8 (2), U3.P$16 (GP12/MISO1/SDA0/TX0)
BTN_NEXT: NEXT.P$1, U3.P$20 (GP15/MOSI1/SCL1)
BTN_PREV: PREV.P$1, U3.P$24 (GP18/SCK0/SDA1)
BTN_RIGHT: SW2.5 (E), U3.P$17 (GP13/CS1/SCL0/RX0)
BTN_SEL: SW2.6 (IN), U3.P$19 (GP14/SCK1/SDA1)
BTN_UP: SW2.1 (N), U3.P$25 (GP19/MOSI0/SCL1)
EINK_BUSY: U3.P$9 (GP6/SCK0/SDA1), U$11.P$1 (EPD_BUSY)
EINK_CS: U3.P$12 (GP9/CS1/SCL0/RX1), U$11.P$4 (EPD_CS)
EINK_DC: U3.P$11 (GP8/MISO1/SDA0/TX1), U$11.P$3 (EPD_DC)
EINK_RST: U3.P$10 (GP7/MOSI0/SCL1), U$11.P$2 (EPD_RESET)
EN: SW1.2, U3.P$37 (3V3_EN)
EN1: R1.3 (1), U1.4 (EN1), U3.P$1 (GP0/MISO0/SDA0/TX0)
EN2: R1.4 (1), U1.3 (EN2), U3.P$29 (GP22)
GND: A0.1, A1.1, BATTERY.1, BTN_LOCK.P$1, C1.2, C2.2, C3.2, C4.2, C5.2, C6.2, D4.A, D5.A, I2C.1 (GND), J1.P6 (VSS), J1.SH1 (SHIELD), J1.SH2 (SHIELD), J1.SH3 (SHIELD), J1.SH4 (SHIELD), JP1.2, NEXT.P$2, PREV.P$2, R1.2 (1), R1.5 (2), R1.6 (2), R2.5 (2), R3.7 (2), R3.8 (2), RESET.P$1, SW1.1, SW2.4 (COM), U1.2 (GND), U2.2 (VSS), U3.P$3 (GND), U3.P$8 (GND), U3.P$13 (GND), U3.P$18 (GND), U3.P$23 (GND), U3.P$28 (GND), U3.P$33 (GND), U3.P$38 (GND), U4.4 (VSS), U$11.P$8 (GND), U$11.P$9 (MP1), U$11.P$10 (MP2)
GP26: D4.C, R4.2, U3.P$31 (GP26/ADC0/SDA1)
GP27: D5.C, R5.2, U3.P$32 (GP27/ADC1/SCL1)
MISO: J1.P7 (DAT0), U3.P$6 (GP4/MISO0/SDA0/TX1), U4.2 (MISO)
MOSI: J1.P3 (CMD), U3.P$5 (GP3/MOSI0/SCL1), U4.5 (MOSI)
MOSI1: U3.P$15 (GP11/MOSI1/SCL1), U$11.P$6 (EPD_MOSI)
unnamed: R2.4 (1), RATE1.1
unnamed: R3.2 (1), RATE2.1
PROG: R3.1, RATE1.2, RATE2.2, U2.5 (PROG)
RESET: RESET.P$2 (S), U3.P$30 (RUN)
RX/SCL: I2C.4 (SCL), JP1.3, R3.4 (1), U3.P$22 (GP17/CS0/SCL0/RX0)
SCK: J1.P5 (CLK), U3.P$4 (GP2/SCK0/SDA1), U4.6 (SCK)
SCK1: U3.P$14 (GP10/SCK1/SDA1), U$11.P$5 (EPD_SCK)
SDCS: J1.P2 (CD/DAT3), R2.3 (1), U3.P$7 (GP5/CS0/SCL0/RX1)
STAT: R1.8 (2), U2.1 (STAT)
STATMON: R1.1, R1.7 (2), U3.P$34 (GP28/ADC2)
SWGND: U3.P$42 (SWGND)
TX/SDA: I2C.3 (SDA), JP1.1, R3.3 (1), U3.P$21 (GP16/MISO0/SDA0/TX0)
V+: C1.1, Q1.2 (S), U1.5 (IN), U3.P$39 (VSYS)
VBAT: BATTERY.2, C4.1, Q1.3 (D), U2.3 (VBAT)
VBUS: Q1.1 (G), U2.4 (VDD), U3.P$40 (VBUS)
_GP26: A0.3, R4.1
_GP27: A1.3, R5.1

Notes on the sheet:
POWER AND FILTERING
10K = 100mA
5.0K = 200mA
3.3K = 300mA
BATTERY CHARGING
FLASH CHIP (FOR UNIFONT)
SERIAL PORT
JST PORTS
SD CARD
E-PAPER DISPLAY

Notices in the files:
Open Book Abridged/OSO-BOOK-C1-01.brd:
CC-BY-SA 4.0
Tiny Book/OSO-TIBO-B2-00.brd:
CC-BY Bon-
parts and their libraries:
COPYRIGHT: Copyright (C) 2018 Accelerated Designs. All rights reserved
